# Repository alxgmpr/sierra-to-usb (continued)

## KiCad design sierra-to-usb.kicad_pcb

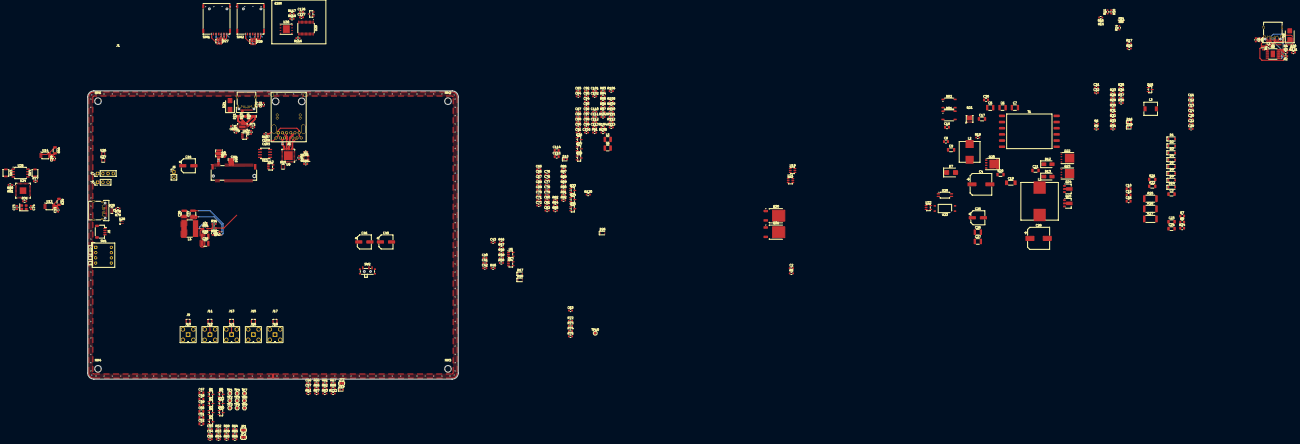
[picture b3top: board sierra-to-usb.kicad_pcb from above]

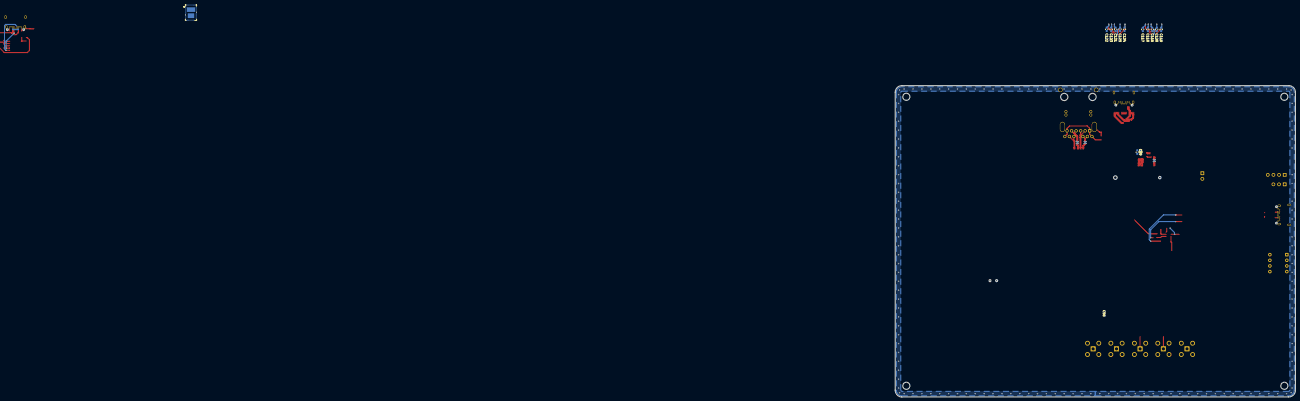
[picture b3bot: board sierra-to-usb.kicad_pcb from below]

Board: 4 copper layers, 180.0 x 140.0 mm, 369 parts (13 on the bottom side), 239 nets.

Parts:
BR1, BR2: MB10S; TSSOP-4_4.4x5mm_P4mm
C1, C71, C82, C94, C102, C127: 1uF; C_0603_1608Metric
C2, C2#2, C62, C63, C109: 1nF; C_0603_1608Metric
C3, C9: 0.1uF/100V; C_1206_3216Metric
C4: 68uF/100V; CP_Elec_10x12.6
C5, C6, C7: 2.2uF/100V; C_1210_3225Metric
C8: 0.1uF/100V; C_0805_2012Metric
C10: 470pF/100V; C_0805_2012Metric
C11: 2.2nF/50V; C_0603_1608Metric
C12: 47nF/50V; C_0603_1608Metric
C13, C14, C34: 0.1uF/25V; C_0603_1608Metric
C15: 0.1uF/50V; C_0805_2012Metric
C16: 1uF/25V; C_0805_2012Metric
C17: 0.047uF/250V; C_1206_3216Metric
C18: 0.22uF/50V; C_0805_2012Metric
C19: 2200pF/2kV; C_1808_4520Metric
C20: 1nF/100V; C_0603_1608Metric
C21, C23: 0.047uF/100V; C_1206_3216Metric
C22, C31: 100pF/25V; C_0603_1608Metric
C24: 1000pF/100V; C_1206_3216Metric
C25: 39uF/16V; CP_Elec_6.3x5.8
C26, C27: 22uF/35V; C_1210_3225Metric
C28: 560uF/25V; CP_Elec_10x10.5
C29: 68nF/16V; C_0603_1608Metric
C30: 1uF/50V; C_0805_2012Metric
C32: 3.9nF/50V; C_0603_1608Metric
C33, C39: 0.1uF/16V; C_0603_1608Metric
C35, C36: 10uF/25V; C_1210_3225Metric
C37, C38: 22uF/16V; C_1210_3225Metric
C40, C41, C42, C43, C60, C61: 1uF/16V; C_0603_1608Metric
C44, C45, C46: 470uF; CP_Elec_6.3x7.7
C47, C48, C49, C50, C51, C52: 10uF; C_0805_2012Metric
C53, C54, C55, C56, C57: 0.1uF; C_0603_1608Metric
C58, C59, C83, C84: 220nF; C_0603_1608Metric
C64, C65, C66, C67, C68, C69, C70, C72, C75, C76, C77, C78, C79, C80, C81, C89, C92, C93, C111, C113, C120, C125, C126: 100nF; C_0603_1608Metric
C73, C74, C85, C86: 27pF; C_0603_1608Metric
C87, C88, C99, C100, C110: 10uF; C_0603_1608Metric
C90, C91, C95, C96, C97, C98, C101: 2.2uF; C_0603_1608Metric
C103: 390pF; C_0603_1608Metric
C112: 10nF; C_0603_1608Metric
C114, C115: 22uF; C_0805_2012Metric
C116, C117, C118, C119, C121, C122, C123, C124: 22pF; C_0603_1608Metric
CN1: EM92xx / RM520N M.2 Key-B (67-pin); M.2_Key-B-SMD_Socket_LOTES_APCI0105-P001A
D1, D2, D3, D4, D5, D8: MMSD914T1G; D_SOD-123
D6: SMAJ13A; D_SMB
D7: SMAJ58A; D_SMB
D9, D14: MMSZ5242B-7-F 12V; D_SOD-123
D10: GREEN; LED_0603_1608Metric
D12, D13: MURA110T3G; D_SMA
D15: BAT54S-7-F; SOT-23
D16: Yellow 0603; LED_0603_1608Metric
D17, D18: B5819W; D_SOD-323
D19: LED_WWAN_STATUS; LED_0603_1608Metric
D20, D21, D22: TPD4EUSB30DQAR; USON-10_2.5x1.0mm_P0.5mm
D23, D25: TPD4E05U06DQAR; USON-10_2.5x1.0mm_P0.5mm
D24: SMAJ5.0A-TR; D_SMB
D26: 1N4148W; D_SOD-323
D27, D28: TPD4S009DBVR; SOT-23-6
D29: Green 0603; LED_0603_1608Metric
D30: Blue 0603; LED_0603_1608Metric
FB1: 33R@100MHz; L_0603_1608Metric
J1, J2, J3: TYPE-C-31-M-04; USB_C_Receptacle_HRO_TYPE-C-31-M-04
J4: SWD; PinHeader_1x03_P2.54mm_Vertical
J5: Qwiic; JST_SH_SM04B-SRSS-TB_1x04-1MP_P1.00mm_Horizontal
J6: Fan; PinHeader_1x02_P2.54mm_Vertical
J7: Spare; PinHeader_1x04_P2.54mm_Vertical
J8: 2250504-1; Bel_2250504-1
J9, J11, J13, J15, J17: CONMHF4-SMD-G-T; MHF4_TE_CONMHF4-SMD-G-T
J10, J12, J14, J16, J18: BWSMA-KE-Z001; SMA_EdgeMount_BWSMA-KE-Z001
JP1, JP2, JP3: SolderJumper_2_Open; SolderJumper-2_P1.3mm_Open_RoundedPad1.0x1.5mm
L1: 15uH; L_Wurth_WE-HCI_74435571500
L2: 5.5uH; L_Wurth_WE-HCI_744325550
L3: 2.2mH; L_6.3x6.3_H3
L4: 2.2uH; L_Bourns-SRN8040_8x8.15mm
L5, L6: 2.2uH; L_1210_3225Metric
MH1, MH2, MH3, MH4: MountingHole_3.2mm_M3
Q1, Q2, Q3, Q4, Q5, Q34, Q35, Q39: 2N7002; SOT-23
Q20: FDMS86250; PQFN-8-EP_6x5mm_P1.27mm_Generic
Q21: FDMC2523P
Q22, Q23: BSC057N08NS3 G; TDSON-8-1
Q24, Q25: FCX493TA; SOT-89-3
Q30, Q31: IRLR7843TRPBF; TO-252-2
Q32, Q33: DMG3415U-7; SOT-23
Q36, Q37, Q38, Q40: BSS138; SOT-23
R1, R67, R120: 1k; R_0603_1608Metric
R2, R4, R53, R55, R57, R64, R65, R66, R102, R105: 10k; R_0603_1608Metric
R3: 24k; R_0603_1608Metric
R5, R5#2, R70, R75, R107: 1M; R_0603_1608Metric
R6: 25.5k; R_0603_1608Metric
R7, R8: 32; R_0805_2012Metric
R9: 15.0k; R_0603_1608Metric
R10: 110k; R_0603_1608Metric
R11, R18, R33, R37, R38, R43, R46, R77, R84: 10.0k; R_0603_1608Metric
R12: 237k; R_0603_1608Metric
R13: 60.4k; R_0603_1608Metric
R14: 49.9k; R_0603_1608Metric
R15: 42.2k; R_0603_1608Metric
R16: 499k; R_0603_1608Metric
R17: 10.0; R_0603_1608Metric
R19: 3.00k; R_0603_1608Metric
R20: 0.05/1W; R_1206_3216Metric
R21: 4.02k; R_1206_3216Metric
R22: 8.06k; R_1206_3216Metric
R23: 2.0k; R_0603_1608Metric
R24: 5.10; R_0805_2012Metric
R25, R26: 10k/1W; R_2512_6332Metric
R27: 100/1W; R_2512_6332Metric
R28: 49.9; R_0603_1608Metric
R29: 40.2k; R_0603_1608Metric
R30: 10.5k; R_0603_1608Metric
R31, R32, R35: 2.00k; R_0603_1608Metric
R34, R36: 1.00k; R_0603_1608Metric
R39, R44: 0.002/1W; R_1206_3216Metric
R40: 36.5k; R_0603_1608Metric
R41: 9.31k; R_0603_1608Metric
R42: 33.2k; R_0603_1608Metric
R45, R47, R48, R49, R50, R51, R52, R54, R56, R58, R62, R63, R68, R72, R82, R85, R87, R88, R89, R90, R91, R116, R119: 100k; R_0603_1608Metric
R59: 33k 1%; R_0603_1608Metric
R60: 18k 1%; R_0603_1608Metric
R61, R92: 330; R_0603_1608Metric
R69: 900k 1%; R_0603_1608Metric
R71: 200k; R_0603_1608Metric
R73, R74: 5.1k; R_0603_1608Metric
R76: 1.0k; R_0603_1608Metric
R78, R79: 27.4; R_0603_1608Metric
R80, R81, R93, R94, R95, R97, R104, R122: 4.7k; R_0603_1608Metric
R86: 22k; R_0603_1608Metric
R96: 2.49k 1%; R_0603_1608Metric
R103: 0R; R_0603_1608Metric
R106: 510; R_0603_1608Metric
R108: 59k 1%; R_0603_1608Metric
R109, R112: 100k 1%; R_0603_1608Metric
R110: 31.6k 1%; R_0603_1608Metric
R111: 10k 1%; R_0603_1608Metric
R113: 20k 1%; R_0603_1608Metric
R117: 20k; R_0603_1608Metric
R121: 560R; R_0603_1608Metric
SIM1, SIM2: XKNANO-113; NanoSIM_XKB_XKNANO-113
SW1: DIP-4; SW_DIP_SPSTx04_Piano_10.8x11.72mm_W7.62mm_P2.54mm
SW2: LED_KILL; SW_SPDT_PCM12
SW3: BOOTSEL; SW_SPST_B3U-1000P
SW4: RUN; SW_SPST_B3U-1000P
T1: 750313355; Transformer_SMT_WE750313355
TP1: FCPO_N; TestPoint_Pad_D1.5mm
TP2: PCIE_DIS; TestPoint_Pad_D1.5mm
TP3: W_DISABLE1_N; TestPoint_Pad_D1.5mm
TP4: MODEM_RESET_N; TestPoint_Pad_D1.5mm
TP5: VBUS_SENSE; TestPoint_Pad_D1.5mm
TP6: WAKE_N; TestPoint_Pad_D1.5mm
TP7: PERST_N; TestPoint_Pad_D1.5mm
TP8: CLKREQ_N; TestPoint_Pad_D1.5mm
TP9: PEWAKE_N; TestPoint_Pad_D1.5mm
TP10: MUX_USB2_SEL; TestPoint_Pad_D1.5mm
U1: HD3SS3220RNHR; Texas_RNH0030A_WQFN-30-1EP_2.5x4.5mm_P0.4mm_EP1.2x3.2mm
U2: CH224K; SSOP-10-1EP_3.9x4.9mm_P1mm_EP2.1x3.3mm
U3: TPS565201DDCR; SOT-23-6
U4, U17: AP2112K-3.3TRG1; SOT-23-5
U5: AP2112K-1.8TRG1; SOT-23-5
U8: TS3USB221DRCR; Texas_S-PVSON-N10
U9: RTL8125BG-CG; QFN-48-1EP_6x6mm_P0.4mm_EP4.3x4.3mm
U10: TPS23730RMTR; TPS23730_RMTR
U11: 93C46; SOIC-8_3.9x4.9mm_P1.27mm
U12: TLV62569DBVR; SOT-23-5
U13, U14: INA226AIDGSR; MSOP-10_3x3mm_P0.5mm
U15: TPS62933FDRLR; SOT-583-8
U19, U21: LM5050MKX-1/NOPB; SOT-23-6
U20: TCMT1107; SOP-4_4.4x2.6mm_P1.27mm
U22: TL431IDBVR; SOT-23-5
U23: FOD817DS; DIP-4_SMD_GullWing_FOD817
U24: RP2040; QFN-56-1EP_7x7mm_P0.4mm_EP3.2x3.2mm
U25: W25Q128JVS; SOIC-8_5.3x5.3mm_P1.27mm
U26, U27: TMP112AIDRLR; SOT-563
U28: SK6805-EC15; LED_SK6805-EC15_1.5x1.5mm
U29: TS3A27518EPWR; TSSOP-24_4.4x7.8mm_P0.65mm
U30: ST4SIM-200M; VFDFPN8_MFF2
Y1: 12MHz; Crystal_SMD_3225-4Pin_3.2x2.5mm
Y2: 25MHz; Crystal_SMD_3225-4Pin_3.2x2.5mm

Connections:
+0V95: C88.1, C96.1, C97.1, C98.1, C99.1, C100.1, C101.1, C102.1, L5.2, R108.1, U9.8 (DVDD09), U9.11 (AVDD09), U9.16 (AVDD09), U9.22 (AVDD09), U9.28 (DVDD09), U9.37 (EVDD09), U9.47 (DVDD09)
+1V8: C41.1, Q32.2 (S), Q36.1 (G), Q37.1 (G), Q38.1 (G), Q40.1 (G), R49.1, R53.1, R55.1, R57.1, R63.1, R64.1, R65.1, R66.1, R68.2, U5.5 (VOUT)
+3V3: C33.1, C37.1, C38.1, C39.1, C40.1, C64.1, D18.2 (A), L4.2, Q33.2 (S), R4.1, R42.1, R44.1, R47.1, R51.1, R82.2, R122.2, U5.1 (VIN), U5.3 (EN), U8.10 (VCC), U13.6 (VS), U14.2 (A0), U14.6 (VS), U14.10 (IN+), U29.8 (VCC)
+3V3_ETH: C87.1, C90.1, C91.1, C92.1, C93.1, C94.1, C95.1, C114.1, C115.1, FB1.1, L6.2, R93.2, R94.2, R95.2, R97.2, R104.2, R106.1, R110.1, U9.19 (AVDD33), U9.29 (DVDD33), U9.33 (AVDD33), U9.34 (AVDD33_XTAL), U9.43 (EVDD33), U9.46 (DVDD33), U11.6 (ORG), U11.8 (VCC), U12.4 (VIN)
+3V3_MCU: C43.1, C65.1, C66.1, C68.1, C69.1, C70.1, C72.1, C75.1, C76.1, C78.1, C79.1, C80.1, C81.1, C82.1, J5.2, J7.3, R77.2, R80.2, R81.2, R84.2, R88.2, R89.2, R90.1, R91.2, U17.5 (VOUT), U24.1 (IOVDD), U24.10 (IOVDD), U24.22 (IOVDD), U24.33 (IOVDD), U24.42 (IOVDD), U24.43 (ADC_AVDD), U24.44 (VREG_VIN), U24.48 (USB_VDD), U24.49 (IOVDD), U25.8 (VCC), U26.5 (V+), U27.4 (ADD0), U27.5 (V+)
+3V3_MOD: C44.1, C45.1, C46.1, C47.1, C48.1, C49.1, C50.1, C51.1, C52.1, C53.1, C54.1, C55.1, C56.1, C57.1, CN1.2 (3.3V), CN1.4 (3.3V), CN1.70 (3.3V), CN1.72 (3.3V), CN1.74 (3.3V), JP1.2 (B), JP2.2 (B), JP3.2 (B), R44.2, U14.8 (VBUS), U14.9 (IN-)
+12V: C110.1, C111.1, D26.1 (K), J6.1, Q30.2 (D), Q31.2 (D), R39.1, R40.1, R45.1, R112.1, U13.10 (IN+), U15.3 (VIN), U19.1 (VS), U19.6 (OUT), U21.1 (VS), U21.6 (OUT)
+12V_BUCK: C35.1, C36.1, R39.2, U3.3 (VIN), U13.8 (VBUS), U13.9 (IN-)
/Ethernet/N_AVDD33_PLL: C89.1, FB1.2, U9.15 (AVDD33_PLL)
/Ethernet/N_BST_ETH: C113.1, U15.6 (BST)
/Ethernet/N_CKXTAL2: R103.1, U9.9 (CKXTAL2)
/Ethernet/N_ETH_EN: R112.2, R113.1, U15.2 (EN)
/Ethernet/N_ETH_SS: C112.1, U15.7 (SS)
/Ethernet/N_EXT095_EN: U9.6 (POW_EXT_SWR), U12.1 (EN)
/Ethernet/N_FB095: R108.2, R109.1, U12.5 (FB)
/Ethernet/N_FB_ETH: R110.2, R111.1, U15.8 (FB)
/Ethernet/N_GPI: R104.1, U9.3 (GPI)
/Ethernet/N_J8_SHIELD: C109.1, J8.SH, R107.1
/Ethernet/N_LED3_A: D10.2 (A), R106.2
/Ethernet/N_PEWAKE_3V3: Q38.3 (D), R95.1, U9.2 (LANWAKEB)
/Ethernet/N_RSET: R96.1, U9.12 (RSET)
/Ethernet/N_SW095: L5.1, U12.3 (SW)
/Ethernet/N_SW_ETH: C113.2, L6.1, U15.5 (SW)
/Ethernet/N_TRCT_COMMON: C103.1, J8.1 (TRCT3), J8.6 (TRCT2), J8.7 (TRCT4), J8.12 (TRCT1)
/Ethernet/N_XTAL1: C86.1, U9.10 (CKXTAL1), Y2.3
/Ethernet/N_XTAL2: C85.1, R103.2, Y2.1
/Ethernet/PCIE_MRX_C_N: C84.1, U9.39 (HSON)
/Ethernet/PCIE_MRX_C_P: C83.1, U9.38 (HSOP)
/Ethernet/RTL_EE_CS: U9.31 (EECS), U11.1 (CS)
/Ethernet/RTL_EE_DO: U9.25 (LED2/EEDO), U11.4 (DO)
/M.2/FCPO_N: CN1.6 (~FULL_CARD_POWER_OFF), Q1.3 (D), R51.2, TP1.1 (1_1)
/M.2/M2_VCC_JP1: CN1.24 (GPIO_7), JP1.1 (A)
/M.2/M2_VCC_JP2: CN1.38 (DEVSLP), JP2.1 (A)
/M.2/M2_VCC_JP3: CN1.68 (SUSCLK), JP3.1 (A)
/M.2/MODEM_RESET_N: CN1.67 (~RESET), Q4.3 (D), R57.2, TP4.1 (1_1)
/M.2/N_LED_A: D19.2 (A), R67.2
/M.2/N_Q6_D: Q32.3 (D), R61.1
/M.2/N_Q6_G: Q5.3 (D), Q32.1 (G), R68.1
/M.2/PCIE_DIS: CN1.20 (GPIO_5), Q2.3 (D), R53.2, TP2.1 (1_1)
/M.2/VBUS_SENSE: CN1.22 (GPIO_6), R59.2, R60.1, R61.2, TP5.1 (1_1)
/M.2/W_DISABLE1_N: CN1.8 (~W_DISABLE1), Q3.3 (D), R55.2, TP3.1 (1_1)
/MCU/DVDD_1V1: C67.1, C71.1, U24.23 (DVDD), U24.45 (VREG_VOUT), U24.50 (DVDD)
/MCU/MCU_GPIO24: J7.1, U24.36 (GPIO24)
/MCU/MCU_GPIO25: J7.2, U24.37 (GPIO25)
/MCU/MCU_SWCLK: J4.1, U24.24 (SWCLK)
/MCU/MCU_SWDIO: J4.2, U24.25 (SWDIO)
/MCU/MCU_USB_DP: R78.1, U24.47 (USB_DP)
/MCU/N_FAN_RTN: D26.2 (A), J6.2, Q34.3 (D)
/MCU/N_LEDKILL_GATE: Q33.1 (G), R82.1, SW2.2 (B)
/MCU/N_SW2_KILL: Q35.3 (D), SW2.1 (A)
/MCU/N_XOUT_R: C74.1, R76.2, Y1.3
/MCU/POE_STATUS: R85.2, R86.1, U24.41 (GPIO29/ADC3)
/MCU/QSPI_SCLK: U24.52 (QSPI_SCLK), U25.6 (CLK)
/MCU/QSPI_SD0: U24.53 (QSPI_SD0), U25.5 (DI/IO_{0})
/MCU/QSPI_SD1: U24.55 (QSPI_SD1), U25.2 (DO/IO_{1})
/MCU/QSPI_SD2: U24.54 (QSPI_SD2), U25.3 (~WP/IO_{2})
/MCU/QSPI_SD3: U24.51 (QSPI_SD3), U25.7 (~HOLD/~RESET/IO_{3})
/MCU/QSPI_SS: SW3.1, U24.56 (~QSPI_SS), U25.1 (~CS)
/MCU/RP2040_RUN: R77.1, SW4.1, U24.26 (RUN)
/MCU/XTAL_XIN: C73.1, U24.20 (XIN), Y1.1
/MCU/XTAL_XOUT: R76.1, U24.21 (XOUT)
/Power Input/+12V_POE: C25.1, C26.1, C27.1, C28.1, D16.2 (A), L1.2, Q31.3 (S), R28.1, U21.4 (IN)
/Power Input/CH224K_CFG1: R3.1, U2.9 (CFG1)
/Power Input/CH224K_PG: D30.1 (K), R4.2, U2.10 (PG)
/Power Input/CH224K_VBUSSENSE: R2.2, U2.8 (VBUS)
/Power Input/CH224K_VDD: C1.1, R1.2, U2.1 (VDD)
/Power Input/J2_SHIELD: C2.1, J2.SH (SHIELD), R5#2.1
/Power Input/N_AUX: D1.2 (A), T1.5 (N3.1)
/Power Input/N_AUX_R: D1.1 (K), D2.1 (K), L3.1
/Power Input/N_BT: U10.12 (BT), U23.2
/Power Input/N_BTLED: R37.2, U23.1
/Power Input/N_BTLED2: D16.1 (K), R38.1
/Power Input/N_C32Z: C32.1, R34.2
/Power Input/N_CLAMP_D: C17.2, Q21.D
/Power Input/N_CLAMP_G: C18.2, D3.2 (A), Q21.G, R18.1
/Power Input/N_CLSA: R7.1, U10.21 (CLSA)
/Power Input/N_CLSB: R8.1, U10.20 (CLSB)
/Power Input/N_COMP: C29.2, R35.2, U10.35 (COMP), U20.4
/Power Input/N_CS: R19.1, U10.1 (CS)
/Power Input/N_CS_SNS: Q20.1 (S), Q20.2 (S), Q20.3 (S), R19.2, R20.1
/Power Input/N_D15COM: C30.1, D15.3 (COM), R33.2
/Power Input/N_D29_A: D29.2 (A), R120.2
/Power Input/N_D30_A: D30.2 (A), R121.1
/Power Input/N_DEN: R6.1, U10.24 (DEN)
/Power Input/N_DT: R15.1, U10.31 (DT)
/Power Input/N_DTHR: C11.1, R12.1, U10.3 (DTHR)
/Power Input/N_FBREF: C31.2, C32.2, R29.2, R30.1, U22.4 (REF)
/Power Input/N_FBTOP: D15.2 (K), R28.2, R29.1, R31.1, R32.1, R33.1
/Power Input/N_FRS: R12.2, R13.1, U10.4 (FRS)
/Power Input/N_GAT2: C18.1, U10.41 (GAT2)
/Power Input/N_GATE: D4.1 (K), R17.1, U10.43 (GATE)
/Power Input/N_GATE_Q: D4.2 (A), Q20.4 (G), R17.2
/Power Input/N_ISTP: R16.1, U10.32 (I_STP)
/Power Input/N_J2_SHIELD: C2#2.1, R5.1
/Power Input/N_LEDA: R31.2, U20.1
/Power Input/N_LINEUV: R10.2, R11.1, U10.38 (LINEUV)
/Power Input/N_PPD: C10.1, R9.1, U10.19 (PPD)
/Power Input/N_Q22_G: D5.2 (A), Q22.4 (G), Q24.3 (E)
/Power Input/N_Q22_RC: C20.1, R24.2
/Power Input/N_Q22_RCD: C21.1, D13.1 (K), R25.1
/Power Input/N_Q23_G: D8.2 (A), Q23.4 (G), Q25.3 (E)
/Power Input/N_Q24_B: D9.1 (K), Q24.1 (B), R21.2, R22.1
/Power Input/N_Q25_B: C22.2, D14.1 (K), Q25.1 (B), R23.2
/Power Input/N_R43C44: C29.1, R36.2
/Power Input/N_REF: R14.1, U10.17 (REF)
/Power Input/N_SEC_CLP: C23.1, D12.1 (K), R26.1
/Power Input/N_SEC_RC: C24.2, R27.1
/Power Input/N_SEC_RTN: C22.1, D8.1 (K), D13.2 (A), Q22.5 (D), Q25.2 (C), R23.1, R24.1, T1.10 (N2.2), T1.11 (N2.2), T1.12 (N2.2)
/Power Input/N_SEC_SW: C24.1, D5.1 (K), D12.2 (A), L1.1, Q23.5 (D), Q24.2 (C), R21.1, T1.7 (N2.1), T1.8 (N2.1), T1.9 (N2.1)
/Power Input/N_SST: C12.1, U10.33 (SST)
/Power Input/N_SW: C17.1, Q20.5 (D), T1.3 (N1.2), T1.4 (N1.2)
/Power Input/N_TLK: C31.1, D15.1 (A), R32.2, R34.1, U20.2, U22.3 (K)
/Power Input/N_U19_GATE: Q30.1 (G), U19.5 (GATE)
/Power Input/N_U21_GATE: Q31.1 (G), U21.5 (GATE)
/Power Input/N_VB: C13.1, R35.1, R36.1, R37.1, U10.34 (FB), U10.37 (VB)
/Power Input/N_VBG: C14.1, U10.40 (VBG)
/Power Input/N_VCC: C15.1, C16.1, L3.2, U10.42 (VCC)
/Power Input/PD_CC1: J2.A5 (CC1), U2.7 (CC1)
/Power Input/PD_CC2: J2.B5 (CC2), U2.6 (CC2)
/Power Input/PD_DM-: J2.A7 (D-), J2.B7 (D-)
/Power Input/PD_DP+: J2.A6 (D+), J2.B6 (D+)
/Power Input/POE_RTN: C3.2, C4.2, C5.2, C6.2, C7.2, C8.2, C11.2, C12.2, C13.2, C14.2, C15.2, C16.2, C19.1, D2.2 (A), D3.1 (K), Q21.S, R11.2, R13.2, R15.2, R16.2, R18.2, R20.2, T1.6 (N3.2), U10.2 (AGND), U10.5 (APD), U10.7 (RTN), U10.8 (RTN), U10.9 (RTN), U10.39 (PSRS), U10.45 (GND), U10.46 (PAD_G), U20.3
/Power Input/POE_VDD54: BR1.3, BR2.3, C3.1, C4.1, D7.1 (K), L2.1, R6.2, R10.1
/Power Input/POE_VDD54_F: C5.1, C6.1, C7.1, C8.1, C9.1, L2.2, T1.1 (N1.1), T1.2 (N1.1), U10.23 (VDD)
/Power Input/POE_VSS: BR1.4, BR2.4, C9.2, C10.2, D7.2 (A), R7.2, R8.2, R9.2, R14.2, U10.27 (VSS), U10.28 (VSS), U10.47 (PAD_S)
/Power Rails/N_OR17: C42.1, D17.1 (K), D18.1 (K), U17.1 (VIN), U17.3 (EN)
/Power Rails/N_U3_FB: R42.2, R43.1, U3.4 (VFB)
/Power Rails/N_U3_SW: C34.2, L4.1, U3.2 (SW)
/Power Rails/N_U3_VBST: C34.1, U3.6 (VBST)
/RF/ANT0: J9.1 (In), J10.1 (In)
/RF/ANT1: J11.1 (In), J12.1 (In)
/RF/ANT2: J13.1 (In), J14.1 (In)
/RF/ANT3: J15.1 (In), J16.1 (In)
/RF/GNSS: J17.1 (In), J18.1 (In)
/SIM/UIM2E_CLK: U29.15 (NO3), U30.6 (CLK)
/SIM/UIM2E_IO: R117.1, U29.17 (NO4), U30.3 (I/O)
/SIM/UIM2E_RST: U29.13 (NO2), U30.7 (RESET)
/SIM/UIM2E_VDD: C126.1, C127.1, R117.2, U29.11 (NO1), U30.8 (VCC)
/SIM/UIM2S_CLK: C122.1, D28.6 (D1-), SIM2.3 (CLK), U29.23 (NC3)
/SIM/UIM2S_DET: C124.1, D28.4 (D2-), SIM2.4 (CD), U29.19 (NC5)
/SIM/UIM2S_IO: C123.1, D28.3 (D2+), SIM2.7 (IO), U29.21 (NC4)
/SIM/UIM2S_RST: C121.1, D28.1 (D1+), SIM2.2 (RST), U29.1 (NC2)
/SIM/UIM2S_VDD: C125.1, D28.5 (VCC), SIM2.1 (VCC), U29.2 (NC1)
/USB2 Debug/USB_DBG_SHIELD: C63.1, R75.1
/USB3 Data/+3V3_MUX: C61.1, R71.2, U1.8 (VCC33), U4.5 (VOUT)
/USB3 Data/CC1_RAW: D23.4 (D2+), U1.2 (CC1)
/USB3 Data/CC2_RAW: C58.1, D23.5 (D2-), U1.1 (CC2), U1.9 (RXP)
/USB3 Data/HD_VBUSDET: R69.2, U1.5 (VBUS_DET)
/USB3 Data/N_J1_SHIELD: C62.1, R70.1
/USB3 Data/N_TXN_PRECAP: C59.1, D21.1 (D1+), D21.10 (NC), U1.10 (RXN), U1.21 (TX2P)
/USB3 Data/N_U1_DIR: R71.1, U1.11 (DIR)
/USB3 Data/SS_CON1_RXN: D20.5 (D2-), U1.14 (RX1N)
/USB3 Data/SS_CON1_RXP: D20.4 (D2+), U1.15 (RX1P)
/USB3 Data/SS_CON1_TXN: D20.2 (D1-), U1.16 (TX1N)
/USB3 Data/SS_CON1_TXP: D20.1 (D1+), U1.17 (TX1P)
/USB3 Data/SS_CON2_RXN: D21.5 (D2-), D21.6 (NC), U1.18 (RX2N)
/USB3 Data/SS_CON2_TXN: D21.2 (D1-), D21.9 (NC), U1.20 (TX2N)
BUCK_EN: R40.2, R41.1, U3.5 (EN)
CLKREQ_N: CN1.52 (~CLKREQ), Q37.2 (S), R65.2, TP8.1 (1_1)
DIP0: R88.1, SW1.1, U24.31 (GPIO20)
DIP1: R89.1, SW1.2, U24.32 (GPIO21)
DIP2: R91.1, SW1.3, U24.34 (GPIO22)
DIP3: R90.2, SW1.4, U24.35 (GPIO23)
FAN_PWM: Q34.1 (G), R87.1, U24.18 (GPIO15)
FCPO_CTL: Q1.1 (G), R52.1, U24.6 (GPIO4)
GND: C1.2, C2.2, C2#2.2, C19.2, C20.2, C21.2, C23.2, C25.2, C26.2, C27.2, C28.2, C30.2, C33.2, C35.2, C36.2, C37.2, C38.2, C39.2, C40.2, C41.2, C42.2, C43.2, C44.2, C45.2, C46.2, C47.2, C48.2, C49.2, C50.2, C51.2, C52.2, C53.2, C54.2, C55.2, C56.2, C57.2, C60.2, C61.2, C62.2, C63.2, C64.2, C65.2, C66.2, C67.2, C68.2, C69.2, C70.2, C71.2, C72.2, C73.2, C74.2, C75.2, C76.2, C77.2, C78.2, C79.2, C80.2, C81.2, C82.2, C85.2, C86.2, C87.2, C88.2, C89.2, C90.2, C91.2, C92.2, C93.2, C94.2, C95.2, C96.2, C97.2, C98.2, C99.2, C100.2, C101.2, C102.2, C103.2, C109.2, C110.2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
I2C_SCL: J5.4, R81.1, U13.5 (SCL), U14.5 (SCL), U24.3 (GPIO1), U26.1 (SCL), U27.1 (SCL)
I2C_SDA: J5.3, R80.1, U13.4 (SDA), U14.4 (SDA), U24.2 (GPIO0), U26.6 (SDA), U27.6 (SDA)
LED0: R105.1, U9.30 (LED0/EEDI), U11.3 (DI)
LED1: R97.1, U9.27 (LED1/EESK), U11.2 (CLK)
LED3: D10.1 (K), U9.35 (LED3)
LED_EN_CTL: Q35.1 (G), R84.1, U24.12 (GPIO9)
LED_PWR: C77.1, Q33.3 (D), R67.1, R120.1, R121.2, U28.2 (VDD)
MDI0_N: J8.10 (TRD1-), U9.14 (MDIN0)
MDI0_P: J8.11 (TRD1+), U9.13 (MDIP0)
MDI1_N: J8.5 (TRD2-), U9.18 (MDIN1)
MDI1_P: J8.4 (TRD2+), U9.17 (MDIP1)
MDI2_N: J8.2 (TRD3-), U9.21 (MDIN2)
MDI2_P: J8.3 (TRD3+), U9.20 (MDIP2)
MDI3_N: J8.9 (TRD4-), U9.24 (MDIN3)
MDI3_P: J8.8 (TRD4+), U9.23 (MDIP3)
MRST_CTL: Q4.1 (G), R58.1, U24.9 (GPIO7)
MUX_USB2_SEL: R72.1, TP10.1 (1_1), U8.9 (S), U24.13 (GPIO10)
N_CLKREQ_3V3: Q37.3 (D), R94.1, U9.48 (CLKREQB), U24.30 (GPIO19)
N_PERST_3V3: Q36.3 (D), R93.1, U9.36 (PERSTB), U24.29 (GPIO18)
unnamed: J1.A1 (GND), J1.A12 (GND), J1.B1 (GND), J1.B12 (GND)
unnamed: J1.A4 (VBUS), J1.A9 (VBUS), J1.B4 (VBUS), J1.B9 (VBUS)
unnamed: J3.A1 (GND), J3.A12 (GND), J3.B1 (GND), J3.B12 (GND)
PCIE_DIS_CTL: Q2.1 (G), R54.1, U24.7 (GPIO5)
PCIE_MRX_N: C84.2, CN1.47 (PETn0/SATA-A-)
PCIE_MRX_P: C83.2, CN1.49 (PETp0/SATA-A+)
PCIE_MTX_N: CN1.41 (PERn0/SATA-B+), U9.42 (HSIN)
PCIE_MTX_P: CN1.43 (PERp0/SATA-B-), U9.41 (HSIP)
PCIE_REFCLK_N: CN1.53 (REFCLKn), U9.45 (REFCLK_N)
PCIE_REFCLK_P: CN1.55 (REFCLKp), U9.44 (REFCLK_P)
PERST_N: CN1.50 (~PERST), Q36.2 (S), R64.2, TP7.1 (1_1)
PEWAKE_N: CN1.54 (~PEWAKE), Q38.2 (S), R66.2, TP9.1 (1_1)
POE_STS_RAW: R38.2, R85.1, U23.4
POE_VA+: BR1.1 (+), J8.13 (VC12)
POE_VA-: BR1.2 (-), J8.14 (VC36)
POE_VB+: BR2.1 (+), J8.15 (VC45)
POE_VB-: BR2.2 (-), J8.16 (VC78)
RGB_DI: R92.1, U24.17 (GPIO14)
RGB_DIN: R92.2, U28.1 (DIN)
RTL_RST_N: R102.1, U9.1 (ISOLATEB), U24.15 (GPIO12)
SIM_SEL: R116.1, U24.14 (GPIO11), U29.14 (IN2), U29.24 (IN1)
SS_MOD_RX_N: CN1.29 (PERn1/USB3.0-Rx-/SSIC-RxN), D22.5 (D2-), U1.7 (TXN)
SS_MOD_RX_P: CN1.31 (PERp1/USB3.0-Rx+/SSIC-RxP), D22.4 (D2+), U1.6 (TXP)
SS_MOD_TX_C_N: C59.2, CN1.35 (PETn1/USB3.0-Tx-/SSIC-TxN), D21.4 (D2+), D21.7 (NC), D22.2 (D1-), U1.19 (RX2P)
SS_MOD_TX_C_P: C58.2, CN1.37 (PETp1/USB3.0-Tx+/SSIC-TxP), D22.1 (D1+)
UIM1_CLK: C117.1, CN1.32 (UIM-CLK), D27.6 (D1-), SIM1.3 (CLK)
UIM1_DET: C119.1, CN1.66 (SIM_DETECT), D27.4 (D2-), SIM1.4 (CD)
UIM1_IO: C118.1, CN1.34 (UIM-DATA), D27.3 (D2+), SIM1.7 (IO)
UIM1_RST: C116.1, CN1.30 (UIM-RESET), D27.1 (D1+), SIM1.2 (RST)
UIM1_VDD: C120.1, CN1.36 (UIM-PWR), D27.5 (VCC), SIM1.1 (VCC)
UIM2_CLK: CN1.44 (GPIO_2), U29.7 (COM3)
UIM2_DET: CN1.40 (GPIO_0), Q39.3 (D), U29.10 (COM5)
UIM2_DET_CTL: Q39.1 (G), R119.1, U24.16 (GPIO13)
UIM2_IO: CN1.42 (GPIO_1), U29.9 (COM4)
UIM2_RST: CN1.46 (GPIO_3), U29.6 (COM2)
UIM2_VDD: CN1.48 (GPIO_4), U29.4 (COM1)
USB2_CON_DM: D23.2 (D1-), U8.2 (1D-)
USB2_CON_DP: D23.1 (D1+), U8.1 (1D+)
USB2_MCU_DM: U8.4 (2D-), U24.5 (GPIO3)
USB2_MCU_DP: U8.3 (2D+), U24.4 (GPIO2)
USB2_MOD_D+: CN1.7 (USB_D+), U8.8 (D+)
USB2_MOD_D-: CN1.9 (USB_D-), U8.7 (D-)
USB_DBG_DM: D25.2 (D1-), R79.2
USB_DBG_DP: D25.1 (D1+), R78.2, R79.1, U24.46 (USB_DM)
VBUSSNS_CTL: Q5.1 (G), R62.1, U24.11 (GPIO8)
VBUS_DATA: C60.1, D24.1 (K), R59.1, R69.1, U1.30 (VDD5), U4.1 (VIN), U4.3 (EN)
VBUS_PD: D6.1 (K), J2.A4 (VBUS), J2.A9 (VBUS), J2.B4 (VBUS), J2.B9 (VBUS), Q30.3 (S), R1.1, R2.1, U19.4 (IN)
VMON_1V8: R49.2, R50.1, U24.40 (GPIO28/ADC2)
VMON_3V3: R47.2, R48.1, U24.39 (GPIO27/ADC1)
VMON_12V: R45.2, R46.1, U24.38 (GPIO26/ADC0)
WAKE_3V3: Q40.3 (D), R122.1, U24.28 (GPIO17)
WAKE_N: CN1.23 (GPIO_11), Q40.2 (S), R63.2, TP6.1 (1_1)
WDIS_CTL: Q3.1 (G), R56.1, U24.8 (GPIO6)
WWAN_LED_N: CN1.10 (GPIO_9/DAS/~DSS/~LED1), D19.1 (K), U24.27 (GPIO16)

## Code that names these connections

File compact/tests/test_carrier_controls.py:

"""Safety-relevant connector and timing topology checks against exported nets."""
from pathlib import Path
import unittest
import xml.etree.ElementTree as ET

class CarrierControls(unittest.TestCase):
    @classmethod
    def setUpClass(cls):
        tree=ET.parse(Path(__file__).resolve().parents[1]/'carrier/build/carrier.xml')
        cls.nets={(p.attrib['ref'],p.attrib['pin']):n.attrib['name'].lstrip('/')
                  for n in tree.findall('.//nets/net') for p in n.findall('node')}

    def pins(self,ref,expected):
        for pin,net in expected.items():
            self.assertEqual(self.nets.get((ref,str(pin))),net,(ref,pin))

    def test_power_requires_source_profile_and_manual_request(self):
        self.pins('U501',{1:'USB_3A_OK',2:'PROFILE_OK',4:'POWER_PERMIT'})
        self.pins('U502',{1:'POWER_PERMIT',2:'POWER_REQUEST',4:'BUCK_ENABLE'})

    def test_control_supply_and_run_are_delayed_after_rail(self):
        self.pins('U503',{1:'MODEM_VCC',2:'GND',3:'BUCK_ENABLE',4:'AUX_3V3',5:'RAIL_DELAY_CT',6:'DRIVE_ALLOWED'})
        self.pins('U504',{1:'MODEM_VCC',2:'GND',3:'DRIVE_ALLOWED',5:'MODEM_CTRL_1V8'})
        self.pins('U506',{1:'MODEM_VCC',3:'RUN_PERMIT',5:'RUN_DELAY_CT',6:'RUN_ALLOWED'})
        self.pins('U507',{2:'RUN_ALLOWED',4:'USB_MUX_OFF'})

    def test_fcpo_and_reset_only_have_open_drain_host_drivers(self):
        self.pins('Q501',{1:'USB_MUX_OFF',2:'GND',3:'FCPO_N'})
        self.pins('Q502',{1:'RESET_PULSE',2:'GND',3:'MODEM_RESET_N'})
        self.pins('U508',{1:'RESET_BUTTON_N',2:'GND',3:'RESET_RSET',4:'RESET_DIV',5:'AUX_3V3',6:'RESET_PULSE'})

    def test_sierra_shutdown_status_is_profile_isolated(self):
        self.pins('J201',{28:'PROFILE_PIN28'})
        self.pins('J202',{17:'PROFILE_PIN28',18:'SIERRA_PLA_STATUS'})

if __name__=='__main__':
    unittest.main()

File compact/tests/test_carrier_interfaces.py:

from pathlib import Path
import unittest
import xml.etree.ElementTree as ET


class CarrierInterfaces(unittest.TestCase):
    @classmethod
    def setUpClass(cls):
        root=ET.parse(Path(__file__).resolve().parents[1]/'carrier/build/carrier.xml')
        cls.nets={(n.attrib['ref'],n.attrib['pin']):net.attrib['name'].lstrip('/')
                  for net in root.findall('.//nets/net') for n in net.findall('node')}

    def test_usb2_switch_has_separate_host_and_modem_ports(self):
        for pin,net in {1:'MOD_USB_D_P',2:'MOD_USB_D_N',5:'GND',6:'USB_MUX_OFF',
                        7:'USB_D_N',8:'USB_D_P',9:'GND',10:'AUX_3V3'}.items():
            self.assertEqual(self.nets.get(('U105',str(pin))),net)

    def test_sim_protection_is_in_module_voltage_domain(self):
        for pin,net in {1:'SIM_VDD',2:'SIM_SOCKET_RST',3:'GND',4:'SIM_SOCKET_CLK',
                        5:'SIM_SOCKET_DATA',8:'GND'}.items():
            self.assertEqual(self.nets.get(('D203',str(pin))),net)

    def test_five_independent_antenna_paths(self):
        for i in range(5):
            net = 'RF_GPS' if i == 4 else f'RF{i+1}'
            mhf, sma = f'J{601+2*i}', f'J{602+2*i}'
            self.assertEqual({p for p, n in self.nets.items() if n == net},
                             {(mhf, '1'), (sma, '1')})
            self.assertEqual(self.nets.get((mhf, '2')), 'GND')
            self.assertEqual(self.nets.get((sma, '2')), 'GND')

    def test_programming_clock_is_accessible(self):
        self.assertEqual(self.nets.get(('J102','3')),'CC_SCL')
        self.assertEqual(self.nets.get(('J102','4')),'CC_SDA')


if __name__=='__main__':
    unittest.main()

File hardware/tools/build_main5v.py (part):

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wire((88.9,81.28),(66.04,81.28));wire((66.04,81.28),(66.04,101.6))
add('Device','R_Small_US','R701','30.1kR',66.04,104.14,fp='Resistor_SMD:R_0603_1608Metric',fields={'MPN':'RC0603FR-0730K1L','Manufacturer':'Yageo','LCSC':'C137745','Tolerance':'1%'})
wire((66.04,106.68),(66.04,114.3));power('GND',(66.04,114.3),'#PWR701')
label('MAIN5V_MODE',(66.04,81.28))
# Feedback divider shares its node with the FB pin using a named local connection.
wire((88.9,76.2),(78.74,76.2));label('MAIN5V_FB',(78.74,76.2));items[-1]=items[-1].replace('justify left bottom','justify right bottom')
for ref,value,mpn,lcsc,y in [('R702','73.2kR','RT0603BRD0773K2L','C861548',43.18),('R703','10kR','RT0603BRD0710KL','C95204',68.58)]:
 add('Device','R_Small_US',ref,value,264.16,y,fp='Resistor_SMD:R_0603_1608Metric',fields={'MPN':mpn,'Manufacturer':'Yageo','LCSC':lcsc,'Tolerance':'0.1%','TCR':'25ppm/K'})
wire((264.16,40.64),(264.16,30.48));label('5V_MAIN',(264.16,30.48))
wire((264.16,45.72),(264.16,66.04));label('MAIN5V_FB',(264.16,58.42))
wire((264.16,71.12),(264.16,81.28));power('GND',(264.16,81.28),'#PWR702')
# AGND and PGND share the electrical return; physical connection follows TI layout guidance.
wire((99.06,88.9),(99.06,99.06));wire((104.14,88.9),(104.14,99.06));wire((99.06,99.06),(104.14,99.06));power('GND',(101.6,99.06),'#PWR703');junction((101.6,99.06))
# Bootstrap capacitor: differential voltage is BOOT-SW, not the rail-to-ground voltage.
add('Device','C_Small','C701','100nF / 25V',139.7,58.42,fp='Capacitor_SMD:C_0603_1608Metric',fields={'MPN':'CL10B104KA8NNNC','Manufacturer':'Samsung Electro-Mechanics','LCSC':'C1590','Dielectric':'X7R','Qualification':'Place immediately between BOOT and SW'})
wire((104.14,63.5),(104.14,45.72));wire((104.14,45.72),(139.7,45.72));wire((139.7,45.72),(139.7,55.88))
wire((139.7,60.96),(139.7,71.12));wire((114.3,71.12),(139.7,71.12));label('MAIN5V_SW',(139.7,71.12))
# Adjustable soft-start capacitor follows the TI reference's 47 nF value.
add('Device','C_Small','C702','47nF / 50V',139.7,104.14,fp='Capacitor_SMD:C_0603_1608Metric',fields={'MPN':'CL10B473KB8NNNC','Manufacturer':'Samsung Electro-Mechanics','LCSC':'C1622','Dielectric':'X7R','Tolerance':'10%','Qualification':'4.7ms typical startup; full timing bounds unqualified'})
wire((114.3,81.28),(139.7,81.28));wire((139.7,81.28),(139.7,101.6));wire((139.7,106.68),(139.7,114.3));power('GND',(139.7,114.3),'#PWR704')
# Input bypass bank: isolated rail only; never raw PoE.
wire((99.06,63.5),(99.06,40.64));label('ISO_12V',(99.06,40.64))
for ref,x in [('C703',210.82),('C704',236.22),('C705',261.62)]:
 bulk=ref!='C705'
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 wire((x,101.6),(x,91.44));wire((x,106.68),(x,116.84))
wire((210.82,91.44),(261.62,91.44));junction((236.22,91.44));wire((236.22,91.44),(236.22,83.82));label('ISO_12V',(236.22,83.82))
wire((210.82,116.84),(261.62,116.84));junction((236.22,116.84));power('GND',(236.22,116.84),'#PWR705')
# Recovery MCU controls EN; external pulldown holds EN low with the GPIO high impedance.
add('Device','R_Small_US','R704','1kR',66.04,68.58,angle=90,fp='Resistor_SMD:R_0603_1608Metric',fields={'MPN':'RC0603FR-071KL','Manufacturer':'Yageo','LCSC':'C22548','Tolerance':'1%'})
items[-1]=re.sub(r'(\(property "Reference" "R704" \(at )[^)]*',r'\g<1>66.04 60.96 90',items[-1])
items[-1]=re.sub(r'(\(property "Value" "1kR" \(at )[^)]*',r'\g<1>66.04 63.5 90',items[-1])
wire((63.5,68.58),(53.34,68.58));label('MCU_MAIN5V_EN',(53.34,68.58));items[-1]=items[-1].replace('(at 53.34 68.58 0)','(at 53.34 68.58 180)').replace('justify left','justify right')
wire((68.58,68.58),(76.2,68.58));wire((76.2,68.58),(76.2,71.12));wire((76.2,71.12),(88.9,71.12));wire((76.2,71.12),(40.64,71.12));junction((76.2,71.12))
add('Device','R_Small_US','R705','10kR',40.64,104.14,fp='Resistor_SMD:R_0603_1608Metric',fields={'MPN':'RC0603FR-0710KL','Manufacturer':'Yageo','LCSC':'C98220','Tolerance':'1%'})
wire((40.64,71.12),(40.64,101.6));wire((40.64,106.68),(40.64,114.3));power('GND',(40.64,114.3),'#PWR706')
# PG is open drain; use the independent recovery supply for the MCU-safe pullup.
add('Device','R_Small_US','R706','10kR',154.94,73.66,fp='Resistor_SMD:R_0603_1608Metric',fields={'MPN':'RC0603FR-0710KL','Manufacturer':'Yageo','LCSC':'C98220','Tolerance':'1%'})
wire((154.94,71.12),(154.94,63.5));power('+3V3',(154.94,63.5),'#PWR707')
wire((114.3,76.2),(154.94,76.2));wire((154.94,76.2),(154.94,81.28));label('MAIN5V_GOOD',(154.94,81.28));junction((154.94,76.2))
# 3.3 uH main power inductor and local output bank; qualification remains open.
add('Device','L_Small','L701','3.3uH',160.02,45.72,angle=90,fp='Inductor_SMD:L_Coilcraft_XAL7070-XXX',fields={'MPN':'XAL7070-332MEC','Manufacturer':'Coilcraft','LCSC':'C3911435','Qualification':'Land pattern audited; hot current margin and AC losses pending'})
wire((139.7,71.12),(144.78,71.12));wire((144.78,71.12),(144.78,45.72));wire((144.78,45.72),(157.48,45.72));junction((139.7,71.12))
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
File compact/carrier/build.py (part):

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c.box('PHYSICAL NANO-SIM / MODULE-SUPPLIED VOLTAGE',15.24,335.28,558.8,66.04)
sim,props=old_symbol('sim','SIM1')
c.place(sim,'J203','XKNANO-113',99.06,368.3,foot=props['Footprint'],fields={'MPN':'XKNANO-113','Manufacturer':'XKB','LCSC':'C381071'})
c.allpins('J203',{1:'SIM_VDD',2:'SIM_SOCKET_RST',3:'SIM_SOCKET_CLK',4:'SIM_DETECT',5:'GND',6:None,7:'SIM_SOCKET_DATA',8:'GND'})
for ref,x,a,b in [('R205',200.66,'SIM_RST','SIM_SOCKET_RST'),('R206',276.86,'SIM_CLK','SIM_SOCKET_CLK'),('R207',353.06,'SIM_DATA','SIM_SOCKET_DATA')]:c.R(ref,'22R',x,360.68,a,b)
c.R('R208','15k',434.34,360.68,'SIM_VDD','SIM_SOCKET_DATA');c.C('C204','100n',518.16,360.68,'SIM_VDD','GND')
c.text('SIM ESD and 10 pF shunts are on the protection sheet; qualify loading and access.',180.34,386.08)
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c.R('R101','1k',246.38,157.48,'USB_VBUS','CC_VBUS_MON')
for ref,x,a in [('C101',365.76,'CC_1V2'),('C102',421.64,'CC_2V7'),('C103',477.52,'USB_VBUS'),('C104',533.4,'AUX_3V3')]:c.C(ref,'1u',x,157.48,a,'GND')
c.text('VSYS uses AUX_3V3 for the 4.0 V carrier-input boundary.\nNVM GPIO_CFG MUST be 10b (DEBUG); default 11b inhibits 3 A enable.\nProgram and read back with external I2C jig before bring-up.',223.52,180.34)
c.box('AUTHORIZATION LOGIC / OPEN-DRAIN DEFAULTS',15.24,215.9,558.8,93.98)
for ref,x,net in [('R102',40.64,'CC_3A_N'),('R103',111.76,'CC_SINK_N'),('R104',182.88,'CC_NO_DEBUG'),('R105',254,'USB_ORIENTATION')]:c.R(ref,'10k',x,246.38,'AUX_3V3',net)
g(norg,'U102',360.68,246.38,'CC_3A_N','CC_SINK_N','USB_SOURCE_3A','C105')
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
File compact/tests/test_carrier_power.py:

"""Independent numeric pin assertions against KiCad's exported netlist."""
from pathlib import Path
import unittest
import xml.etree.ElementTree as ET


class CarrierPower(unittest.TestCase):
    @classmethod
    def setUpClass(cls):
        root = ET.parse(Path(__file__).resolve().parents[1] / 'carrier/build/carrier.xml')
        cls.nets = {
            (n.attrib['ref'], n.attrib['pin']): net.attrib['name'].lstrip('/')
            for net in root.findall('.//nets/net') for n in net.findall('node')
        }

    def test_protected_auxiliary_supply(self):
        # TPS259470 RPW pin table; TPS7A2033 DBV pin table.
        for endpoint, net in {
            ('U301', '5'): 'USB_VBUS', ('U301', '6'): 'PROTECTED_VBUS',
            ('U301', '8'): 'GND', ('U302', '1'): 'SENSED_VBUS',
            ('U302', '2'): 'GND', ('U302', '3'): 'SENSED_VBUS',
            ('U302', '5'): 'AUX_3V3',
        }.items():
            with self.subTest(endpoint=endpoint):
                self.assertEqual(self.nets.get(endpoint), net)

    def test_input_current_sense_polarity(self):
        # INA190A1 DCK, SBOS863D p3: REF/GND/VS/IN+/IN-/OUT.
        expected = {1:'GND',2:'GND',3:'AUX_3V3',4:'INPUT_SENSE_P',
                    5:'INPUT_SENSE_N',6:'INPUT_CURRENT_MON'}
        for pin, net in expected.items():
            with self.subTest(pin=pin):
                self.assertEqual(self.nets.get(('U303',str(pin))),net)

    def test_buck_power_pins_and_passive_current_override(self):
        # ADI LTC3310S Rev F p10; ITH is the current-command node.
        for pin in (3,4,11,12):
            self.assertEqual(self.nets.get(('U401',str(pin))),'SENSED_VBUS')
        for pin in (5,10,19):
            self.assertEqual(self.nets.get(('U401',str(pin))),'GND')
        for pin in (6,7,8,9):
            self.assertEqual(self.nets.get(('U401',str(pin))),'BUCK_SW')
        self.assertEqual(self.nets.get(('U401','1')),'BUCK_ENABLE')
        self.assertEqual(self.nets.get(('U401','17')),'BUCK_ITH')
        self.assertEqual(self.nets.get(('D401','2')),'BUCK_ITH')
        self.assertEqual(self.nets.get(('D401','1')),'CURRENT_CLAMP')


class KelvinShunt(unittest.TestCase):
    def test_sense_paths_do_not_share_force_nets(self):
        tree=ET.parse(Path(__file__).resolve().parents[1]/'carrier/build/carrier.xml')
        nets={(p.attrib['ref'],p.attrib['pin']):n.attrib['name'].lstrip('/')
              for n in tree.findall('.//nets/net') for p in n.findall('node')}
        for pin,net in {1:'PROTECTED_VBUS',2:'SENSED_VBUS',3:'INPUT_SENSE_P',4:'INPUT_SENSE_N'}.items():
            self.assertEqual(nets.get(('R307',str(pin))),net)
        self.assertEqual(nets[('U303','4')],'INPUT_SENSE_P')
        self.assertEqual(nets[('U303','5')],'INPUT_SENSE_N')

if __name__ == '__main__':
    unittest.main()

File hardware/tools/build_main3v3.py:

#!/usr/bin/env python3
"""Generate the reviewed always-on supply draft from unmodified KiCad symbols."""
from pathlib import Path
import re, uuid
ROOT=Path(__file__).resolve().parents[1]
LIB=Path('/Applications/KiCad/KiCad.app/Contents/SharedSupport/symbols')
NS=uuid.UUID('d93a1f6c-985a-4f01-8a3e-c4e66e488ac0')
def uid(key):return str(uuid.uuid5(NS,key))
def block(text,start):
 depth=0; quoted=False; escape=False
 for i in range(start,len(text)):
  c=text[i]
  if escape:escape=False;continue
  if c=='\\' and quoted:escape=True;continue
  if c=='"':quoted=not quoted
  if not quoted:
   if c=='(':depth+=1
   elif c==')':
    depth-=1
    if depth==0:return text[start:i+1]
 raise ValueError('Unbalanced S expression')
def library(lib,name):
 text=(LIB/(lib+'.kicad_sym')).read_text()
 match=re.search(r'\(symbol "'+re.escape(name)+r'"\s',text)
 assert match,(lib,name)
 s=block(text,match.start())
 assert '(extends ' not in s,'Use a resolved standard symbol'
 return s.replace('(symbol "'+name+'"','(symbol "'+lib+':'+name+'"',1)
used={};items=[];counter=0
font='(effects (font (size 1.27 1.27)))'
def prop(name,value,x,y,hide=False):
 return f'(property "{name}" "{value}" (at {x} {y} 0) (effects (font (size 1.27 1.27))'+(' (hide yes)' if hide else '')+'))'
def add(lib,name,ref,value,x,y,angle=0,fp='',fields=None):
 key=lib+':'+name
 if key not in used:used[key]=library(lib,name)
 s=used[key]
 pins=re.findall(r'\(number "([^"]+)"',s)
 assert len(pins)==len(set(pins)),(ref,pins)
 if ref.startswith('#'):
  properties=prop('Reference',ref,x,y,True)+prop('Value',value,x,y+(3.81 if name=='GND' else -3.81),ref.startswith('#FLG'))
 elif ref.startswith('U'):
  properties=prop('Reference',ref,x,y-15)+prop('Value',value,x,y-12)
 elif ref.startswith('L'):
  properties=prop('Reference',ref,x,y-6.35)+prop('Value',value,x,y-3.81)
 else:
  properties=prop('Reference',ref,x+8.89,y-1.27)+prop('Value',value,x+12.7,y+1.27)
 if ref.startswith('L'):
  properties=re.sub(r'(\(at [^()]+) 0\)',r'\1 90)',properties)
 if ref.startswith('C'):
  properties=prop('Reference',ref,x-10.16,y-1.27)+prop('Value',value,x-10.16,y+1.27)
  properties=properties.replace('(effects (font (size 1.27 1.27)))','(effects (font (size 1.27 1.27)) (justify right))')
 properties+=prop('Footprint',fp,x,y,True)
 for k,v in (fields or {}).items():properties+=prop(k,v,x,y,True)
 items.append(f'(symbol (lib_id "{key}") (at {x} {y} {angle}) (unit 1) (in_bom '+('no' if ref.startswith('#') else 'yes')+') (on_board yes) (dnp no) (uuid "'+uid(ref)+'") '+properties+' '+''.join(f'(pin "{p}" (uuid "{uid(ref+":"+p)}"))' for p in pins)+f' (instances (project "main3v3" (path "/{uid("root")}" (reference "{ref}") (unit 1)))))')
 return {num:(float(px),float(py)) for px,py,num in re.findall(r'\(pin .*?\(at ([\d.\-]+) ([\d.\-]+) [\d.\-]+\).*?\(number "([^"]+)"',s,re.S)}
def wire(a,b):
 a=tuple(round(v,4) for v in a);b=tuple(round(v,4) for v in b)
 global counter
 counter+=1
 items.append(f'(wire (pts (xy {a[0]} {a[1]}) (xy {b[0]} {b[1]})) (stroke (width 0) (type default)) (uuid "{uid("wire"+str(counter))}"))')
def junction(p):items.append(f'(junction (at {p[0]} {p[1]}) (diameter 0) (color 0 0 0 0) (uuid "{uid("junction"+str(p))}"))')
def label(name,p):
 if name in {'5V_MAIN','3V3_MAIN','MAIN3V3_GOOD'}:
  items.append(f'(global_label "{name}" (shape passive) (at {p[0]} {p[1]} 0) (effects (font (size 1.27 1.27)) (justify left)) (uuid "{uid("global"+name+str(p))}"))');return
 items.append(f'(label "{name}" (at {p[0]} {p[1]} 0) (effects (font (size 1.27 1.27)) (justify left bottom)) (uuid "{uid("label"+name+str(p))}"))')
def power(name,p,ref):add('power',name,ref,name,*p)
def note(text,p,size=1.27):items.append(f'(text "{text}" (at {p[0]} {p[1]} 0) (effects (font (size {size} {size})) (justify left)) (uuid "{uid(text)}"))')
def pinlabel(number,name):
 px,py=pins[number]; a=(101.6+px,76.2-py);b=(a[0]+(-7.62 if px<0 else 7.62),a[1]);wire(a,b);power('+3V3',b,'#PWR413') if name=='+3V3' else label(name,b)


raw=(ROOT/'Recovery.kicad_sym').read_text()
used['Recovery:MP2143DJ-LF-Z']=block(raw,raw.index('(symbol "MP2143DJ-LF-Z"')).replace('(symbol "MP2143DJ-LF-Z"','(symbol "Recovery:MP2143DJ-LF-Z"',1)
add('Recovery','MP2143DJ-LF-Z','U601','MP2143DJ-LF-Z',101.6,76.2,fp='Package_TO_SOT_SMD:TSOT-23-8',fields={'MPN':'MP2143DJ-LF-Z','Manufacturer':'Monolithic Power Systems','LCSC':'C43427'})
wire((101.6,66.04),(101.6,50.8));label('5V_MAIN',(101.6,50.8))
wire((91.44,73.66),(78.74,73.66));label('MAIN3V3_EN',(78.74,73.66));items[-1]=items[-1].replace('justify left bottom','justify right bottom')
wire((111.76,78.74),(124.46,78.74));label('MAIN3V3_PG_5V',(124.46,78.74))
for x in [99.06,104.14]:wire((x,86.36),(x,93.98))
wire((99.06,93.98),(104.14,93.98));power('GND',(101.6,93.98),'#PWR601')
add('Device','L','L601','1uH',139.7,73.66,angle=90,fp='Inductor_SMD:L_Coilcraft_XxL4030',fields={'MPN':'XGL4030-102MEC','Manufacturer':'Coilcraft','LCSC':'C6336766','Qualification':'Footprint dimensions and hot saturation pending'})
wire((111.76,73.66),(135.89,73.66));wire((143.51,73.66),(175.26,73.66));label('3V3_MAIN',(175.26,73.66))
wire((91.44,78.74),(83.82,78.74));label('3V3_MAIN',(83.82,78.74));items[-1]=items[-1].replace('(at 83.82 78.74 0)','(at 83.82 78.74 180)').replace('justify left','justify right')
cap={'MPN':'CL32B226KAJNNNE','Manufacturer':'Samsung Electro-Mechanics','LCSC':'C309062','Qualification':'Bank sizing and loop stability pending'}
for ref,x,y,net in [('C601',55.88,63.5,'5V_MAIN'),('C602',175.26,91.44,'3V3_MAIN'),('C603',200.66,91.44,'3V3_MAIN')]:
 add('Device','C_Small',ref,'22uF / 25V',x,y,fp='Capacitor_SMD:C_1210_3225Metric',fields=cap)
 wire((x,y-2.54),(x,y-10.16));label(net,(x,y-10.16));wire((x,y+2.54),(x,y+10.16));power('GND',(x,y+10.16),'#PWR62'+ref[1:])
for ref,value,mpn,lcsc,y in [('R601','200kR','RT0603BRD07200KL','C728585',127),('R602','44.2kR','RT0603BRD0744K2L','C861410',142.24)]:
 add('Device','R_Small_US',ref,value,139.7,y,fp='Resistor_SMD:R_0603_1608Metric',fields={'MPN':mpn,'Manufacturer':'Yageo','LCSC':lcsc,'Tolerance':'0.1%','TCR':'25ppm/C'})
wire((139.7,124.46),(139.7,116.84));label('3V3_MAIN',(139.7,116.84))
wire((139.7,129.54),(139.7,139.7));label('MAIN3V3_FB',(139.7,134.62))
wire((91.44,76.2),(83.82,76.2));label('MAIN3V3_FB',(83.82,76.2));items[-1]=items[-1].replace('justify left bottom','justify right bottom')
wire((139.7,144.78),(139.7,152.4));power('GND',(139.7,152.4),'#PWR610')
# Reference enable divider: rail follows upstream 5 V without a PMIC dependency.
for ref,value,mpn,lcsc,y in [('R603','20kR','RC0603FR-0720KL','C105575',127),('R604','10kR','RC0603FR-0710KL','C98220',142.24)]:
 add('Device','R_Small_US',ref,value,210.82,y,fp='Resistor_SMD:R_0603_1608Metric',fields={'MPN':mpn,'Manufacturer':'Yageo','LCSC':lcsc,'Tolerance':'1%'})
wire((210.82,124.46),(210.82,116.84));label('5V_MAIN',(210.82,116.84))
wire((210.82,129.54),(210.82,139.7));label('MAIN3V3_EN',(210.82,134.62))
wire((210.82,144.78),(210.82,152.4));power('GND',(210.82,152.4),'#PWR611')
# 5 V tolerant Schmitt input, powered by the independent recovery supply.
add('74xGxx','74LVC1G17','U602','SN74LVC1G17DBVR',210.82,45.72,fp='Package_TO_SOT_SMD:SOT-23-5',fields={'MPN':'SN74LVC1G17DBVR','Manufacturer':'Texas Instruments','LCSC':'C7836'})
items[-1]=items[-1].replace('(at 210.82 30.72 0)','(at 210.82 22.86 0)').replace('(at 210.82 33.72 0)','(at 210.82 25.4 0)')
wire((198.12,45.72),(185.42,45.72));label('MAIN3V3_PG_5V',(185.42,45.72));items[-1]=items[-1].replace('justify left bottom','justify right bottom')
wire((220.98,45.72),(233.68,45.72));label('MAIN3V3_GOOD',(233.68,45.72))
power('+3V3',(205.74,35.56),'#PWR612');power('GND',(205.74,55.88),'#PWR613')
add('Device','C_Small','C604','100nF / 25V',254,66.04,fp='Capacitor_SMD:C_0603_1608Metric',fields={'MPN':'CL10B104KA8NNNC','Manufacturer':'Samsung Electro-Mechanics','LCSC':'C1590'})
power('+3V3',(254,63.5),'#PWR614');power('GND',(254,68.58),'#PWR615')
for ref,value,mpn,lcsc,y in [('R605','10kR','RC0603FR-0710KL','C98220',127),('R606','100kR','RC0603FR-07100KL','C14675',142.24)]:
 add('Device','R_Small_US',ref,value,254,y,fp='Resistor_SMD:R_0603_1608Metric',fields={'MPN':mpn,'Manufacturer':'Yageo','LCSC':lcsc,'Tolerance':'1%'})
wire((254,124.46),(254,116.84));label('5V_MAIN',(254,116.84))
wire((254,129.54),(254,139.7));label('MAIN3V3_PG_5V',(254,134.62))
wire((254,144.78),(254,152.4));power('GND',(254,152.4),'#PWR616')
note('Main sequencing and PG translation captured; capacitance and thermal margins unqualified.',(35.56,172.72))
# Switching output is behind a passive filter inductor.
power('PWR_FLAG',(175.26, 73.66),'#FLG601')
(ROOT/'main3v3.kicad_sch').write_text('(kicad_sch (version 20250114) (generator eeschema) (uuid "'+uid('root')+'") (paper "A4") (lib_symbols '+''.join(used.values())+') '+''.join(items)+')\n')
print('Generated main 3.3V draft')

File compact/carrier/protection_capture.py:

"""USB isolation, connector ESD, module-powered SIM and programming access."""


def capture(c,ic,put):
    c.reset_sheet('protection')
    c.box('USB2 ISOLATION / BOTH DATA SWITCHES DISABLED DURING OFF STATE',15.24,15.24,558.8,91.44)
    sw=ic('TS3USB221ARSER',[(1,'1D+','bidirectional','R'),(2,'1D-','bidirectional','R'),
        (3,'2D+','bidirectional','R'),(4,'2D-','bidirectional','R'),(5,'GND','power_in','B'),
        (6,'OE_N','input','L'),(7,'D-','bidirectional','L'),(8,'D+','bidirectional','L'),
        (9,'S','input','L'),(10,'VCC','power_in','T')],
        'Package_DFN_QFN:Texas_UQFN-10_1.5x2mm_P0.5mm',
        'https://www.ti.com/lit/ds/symlink/ts3usb221a.pdf')
    put(sw,'U105',104.14,60.96,{1:'MOD_USB_D_P',2:'MOD_USB_D_N',3:None,4:None,5:'GND',
        6:'USB_MUX_OFF',7:'USB_D_N',8:'USB_D_P',9:'GND',10:'AUX_3V3'})
    c.C('C108','100n',215.9,60.96,'AUX_3V3','GND')
    c.R('R106','10k',292.1,60.96,'AUX_3V3','USB_MUX_OFF')
    c.text('S=0 selects 1D pair; OE_N=1 isolates host and modem.\nPower-off leakage specified by TI: +/-2 uA with VCC=0.\nUSB3 uses the same USB_MUX_OFF command.\nValidate detach, brownout and asymmetric rail collapse on hardware.',353.06,43.18)

    c.box('CONNECTOR-SIDE ESD / PLACE BEFORE USB SWITCHES',15.24,119.38,558.8,114.3)
    def esd(part,ref,x,nets):
        pinlist=[(1,'D1+','passive','L'),(2,'D1-','passive','L'),(3,'GND','passive','B'),
                 (4,'D2+','passive','L'),(5,'D2-','passive','L'),(8,'GND','passive','B')]
        pinlist += [(n,'NC','no_connect','R') for n in (6,7,9,10)]
        symbol=ic(part,pinlist,'Package_SON:USON-10_2.5x1.0mm_P0.5mm',
                  'https://www.ti.com/lit/ds/symlink/'+('tpd4eusb30' if 'USB30' in part else 'tpd4e05u06')+'.pdf')
        put(symbol,ref,x,165.1,{1:nets[0],2:nets[1],3:'GND',4:nets[2],5:nets[3],8:'GND',
                              6:None,7:None,9:None,10:None})
    esd('TPD4EUSB30DQAR','D101',111.76,['C_TX1_P','C_TX1_N','C_RX1_P','C_RX1_N'])
    esd('TPD4EUSB30DQAR','D102',299.72,['C_TX2_P','C_TX2_N','C_RX2_P','C_RX2_N'])
    esd('TPD4E05U06DQAR','D103',487.68,['CC1','CC2','USB_D_P','USB_D_N'])
    c.text('Each SS pair uses matched channels. Shield and ESD returns need a short ground path.\nNC pads are left electrically unconnected in this capture. Route protected pads without branch stubs.\nChannel/connector insertion loss and system ESD performance require qualification.',30.48,205.74)

    c.box('SIM PROTECTION / MODULE-SUPPLIED VOLTAGE ONLY',15.24,246.38,558.8,68.58)
    # Same numeric DQA pin map as the connector-side array above.
    symbol='carrier-parts:TPD4E05U06DQAR'
    put(symbol,'D203',99.06,284.48,{1:'SIM_VDD',2:'SIM_SOCKET_RST',3:'GND',
        4:'SIM_SOCKET_CLK',5:'SIM_SOCKET_DATA',8:'GND',6:None,7:None,9:None,10:None})
    for ref,x,net in [('C205',231.14,'SIM_SOCKET_RST'),('C206',337.82,'SIM_SOCKET_CLK'),
                      ('C207',444.5,'SIM_SOCKET_DATA')]:
        c.C(ref,'10p C0G',x,284.48,net,'GND')

    c.box('EXTERNAL CC NVM PROGRAMMING / TEST ACCESS',15.24,327.66,558.8,58.42)
    c.place('Connector_Generic:Conn_01x04','J102','I2C PROGRAM / USB POWERED',99.06,360.68,
        foot='Connector_PinHeader_2.54mm:PinHeader_1x04_P2.54mm_Vertical',
        fields={'MPN':'TSW-104-07-G-S','Manufacturer':'Samtec'})
    c.allpins('J102',{1:'GND',2:'AUX_3V3',3:'CC_SCL',4:'CC_SDA'})
    c.R('R107','4.7k',241.3,358.14,'AUX_3V3','CC_SCL')
    c.R('R108','4.7k',330.2,358.14,'AUX_3V3','CC_SDA')
    c.text('Pin 2 is target-voltage reference, not programmer power input.\nUse 3.3 V open-drain I2C with USB supplying the target.\nProgram DEBUG GPIO configuration; read back before enabling modem.',396.24,350.52)
    return c.save_sheet('protection','USB and SIM protection, USB2 isolation and CC programming')
